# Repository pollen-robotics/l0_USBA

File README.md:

# l0_USBA
This repository contains the KiCad project of the board used to connect the different modules of Reachy with USB to a computer.

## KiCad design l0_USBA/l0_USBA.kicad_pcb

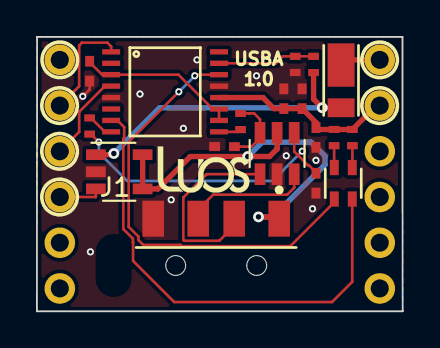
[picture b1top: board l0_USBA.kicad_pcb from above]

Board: 2 copper layers, 20.3 x 15.2 mm, 19 parts (0 on the bottom side), 20 nets.

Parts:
C1, C2: 47pF; C_0402_NoSilk
C3, C4, C5: 100nF; C_0402_NoSilk
C6: 4.7uF; C_0402_NoSilk
D1: KPTB-1615ESGC
D2: DFLS230L-7; PowerDI-123
J1: USB_A; Molex-48037-1000-0
J2: l0_Shield_Socket
R1, R2: 27; R_0402_NoSilk
R3: 4K7; R_0402_NoSilk
R4: 10K; R_0402_NoSilk
R5: 66,5; R_0402_NoSilk
R6: 56; R_0402_NoSilk
U1: FT230X; SSOP-16
U2: STMPS2171STR; SOT-23-5
U3: USBLC6-2SC6; SOT23-6L

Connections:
+3V3: C4.1, C5.1, C6.1, J2.5, R5.1, R6.1, U1.12
+5V: J1.1, U2.4, U2.5, U3.5
/RxD: J2.9, U1.4
/Rx_LED: D1.4, U1.7
/TxD: J2.8, U1.1
/Tx_LED: D1.2, U1.14
/Vin: D2.1, J2.6
GND: C1.2, C2.2, C3.2, C4.2, C5.2, C6.2, J1.4, J2.7, R4.1, U1.5, U1.13, U2.2, U3.2
unnamed: C1.1, R2.2, U3.6
unnamed: C2.1, R1.2, U3.4
unnamed: C3.1, U1.3, U1.10, U1.11
unnamed: D1.1, R5.2
unnamed: D1.3, R6.2
unnamed: J1.2, U3.1
unnamed: J1.3, U3.3
unnamed: J2.10, U2.3
unnamed: R1.1, U1.8
unnamed: R2.1, U1.9
unnamed: R3.1, R4.2, U1.15
VBUS: D2.2, R3.2, U2.1

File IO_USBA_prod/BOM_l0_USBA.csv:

Reference,Quantity,Value,Footprint,Datasheet,CodeCommande,Fournisseur
C1 C2,2,47pF,Common_Footprint:C_0402_NoSilk,,2496804,Farnell
C3 C4 C5,3,100nF,Common_Footprint:C_0402_NoSilk,,2524735,Farnell
C6,1,4.7uF,Common_Footprint:C_0402_NoSilk,,1735525,Farnell
D1,1,KPTB-1615ESGC,Common_Footprint:KPTB-1615ESGC,http://www.farnell.com/datasheets/2046076.pdf?_ga=2.11215303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,2426236,Farnell
D2,1,DFLS230L-7,Common_Footprint:PowerDI-123,~,1858663,Farnell
J1,1,USB_A,EEC:Molex-48037-1000-0,,2751683,Farnell
J2,0,l0_Shield_Socket,Common_Footprint:l0_Shield_Socket,,,
R1 R2,2,27,Common_Footprint:R_0402_NoSilk,,2447146,Farnell
R3,1,4K7,Common_Footprint:R_0402_NoSilk,,2447187,Farnell
R4,1,10K,Common_Footprint:R_0402_NoSilk,,2447096,Farnell
R5,1,"66,5",Common_Footprint:R_0402_NoSilk,,2073198,Farnell
R6,1,56,Common_Footprint:R_0402_NoSilk,,2073128,Farnell
U1,1,FT230X,Common_Footprint:SSOP-16,,2081321,Farnell
U2,1,STMPS2171STR,Common_Footprint:SOT-23-5,http://www.farnell.com/datasheets/1700527.pdf?_ga=2.25944167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,2762726,Farnell
U3,1,USBLC6-2SC6,Common_Footprint:SOT23-6L,http://www2.st.com/resource/en/datasheet/CD00050750.pdf,1269406,Farnell

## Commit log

2021-06-08 Initial commit.
2023-06-26 Update prod folder.
